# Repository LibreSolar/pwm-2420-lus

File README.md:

# PWM Solar Charge Controller (10-20A)

 Tested prototype, only minor issues left.

This PWM charge controller is cheaper than the MPPT charge controllers, as it does not contain the internal powerful DC/DC converter necessary for MPPT. The lower production cost and easy manufacturing with larger SMD components makes it ideally suited for solar home systems (SHS) for rural electrification.

The design allows to use either SMD MOSFETs or TO220 THT MOSFETs, which can be easily attached to a heat sink.

Schematic: [PDF file](pwm-2420-lus.pdf) in repository

Gerber files: [PCB ordering](http://libre.solar/docs/pcb_ordering) documentation

Bill of Materials: [BOM export](http://libre.solar/docs/bom) from KiCAD

Firmware: [Charge Controller Firmware](https://github.com/LibreSolar/charge-controller-firmware) repository

## Features:
- 12V/24V battery voltage
- Up to 20A max. charge current (depending on selected MOSFETs)
- 55V max. solar input
- 32bit ARM MCU (STM32L072)
- Expandable via Olimex Universal Extension Connector (UEXT) featuring
   I2C, Serial and SPI interface (e.g. used for display, WIFI communication, etc.)
- USB charging (single port)
- Low-side load switching

## Built-in protection
- Overvoltage
- Undervoltage
- Overcurrent
- PV short circuit
- PV reverse polarity (for max. module open circuit voltage of around 40V)
- Battery reverse polarity

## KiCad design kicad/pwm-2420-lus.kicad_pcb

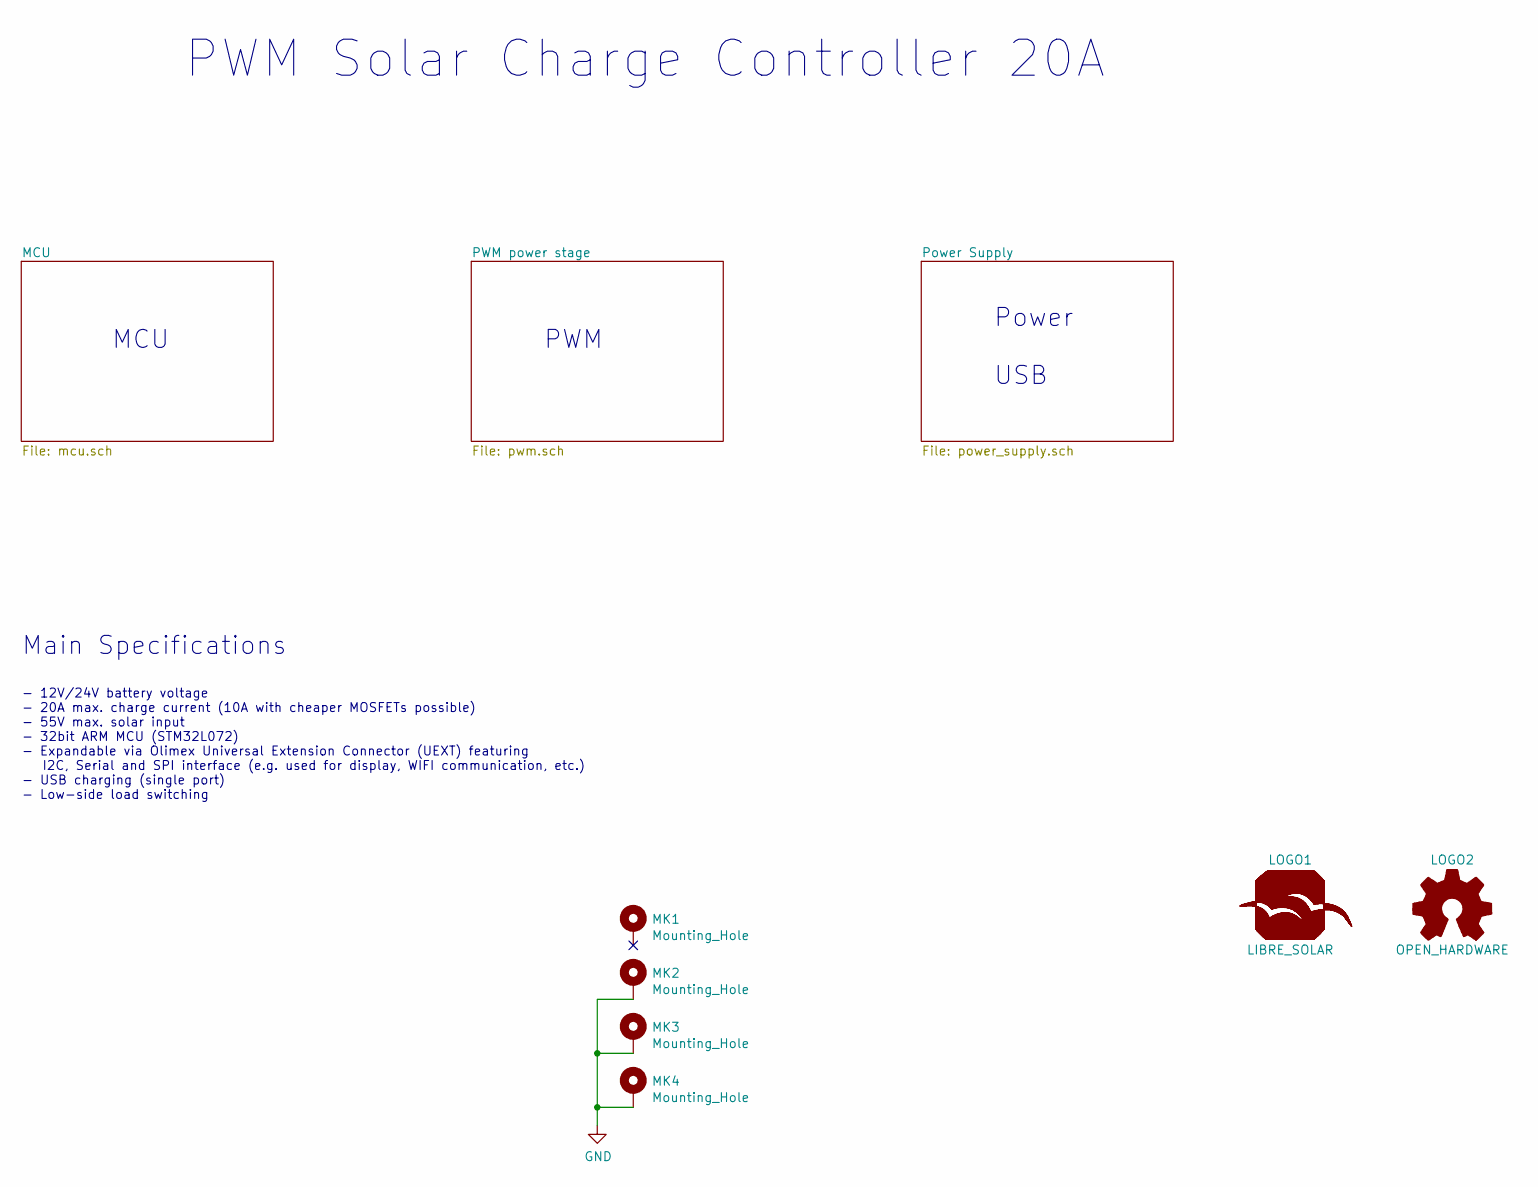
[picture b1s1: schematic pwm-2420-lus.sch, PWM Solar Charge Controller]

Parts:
LOGO1: LIBRE_SOLAR; LIBRESOLAR_LOGO
LOGO2: OPEN_HARDWARE; OSHW-Logo_5.7x6mm_SilkScreen
MK1, MK2, MK3, MK4: Mounting_Hole; MountingHole_3.2mm_M3_Pad

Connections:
GND: MK2.1, MK3.1, MK4.1; also elsewhere on the board

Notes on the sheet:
PWM Solar Charge Controller 20A
Main Specifications
- 12V/24V battery voltage - 20A max. charge current (10A with cheaper MOSFETs possible) - 55V max. solar input - 32bit ARM MCU (STM32L072) - Expandable via Olimex Universal Extension Connector (UEXT) featuring I2C, Serial and SPI interface (e.g. used for display, WIFI communication, etc.) - USB cha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
PWM
MCU
Power USB

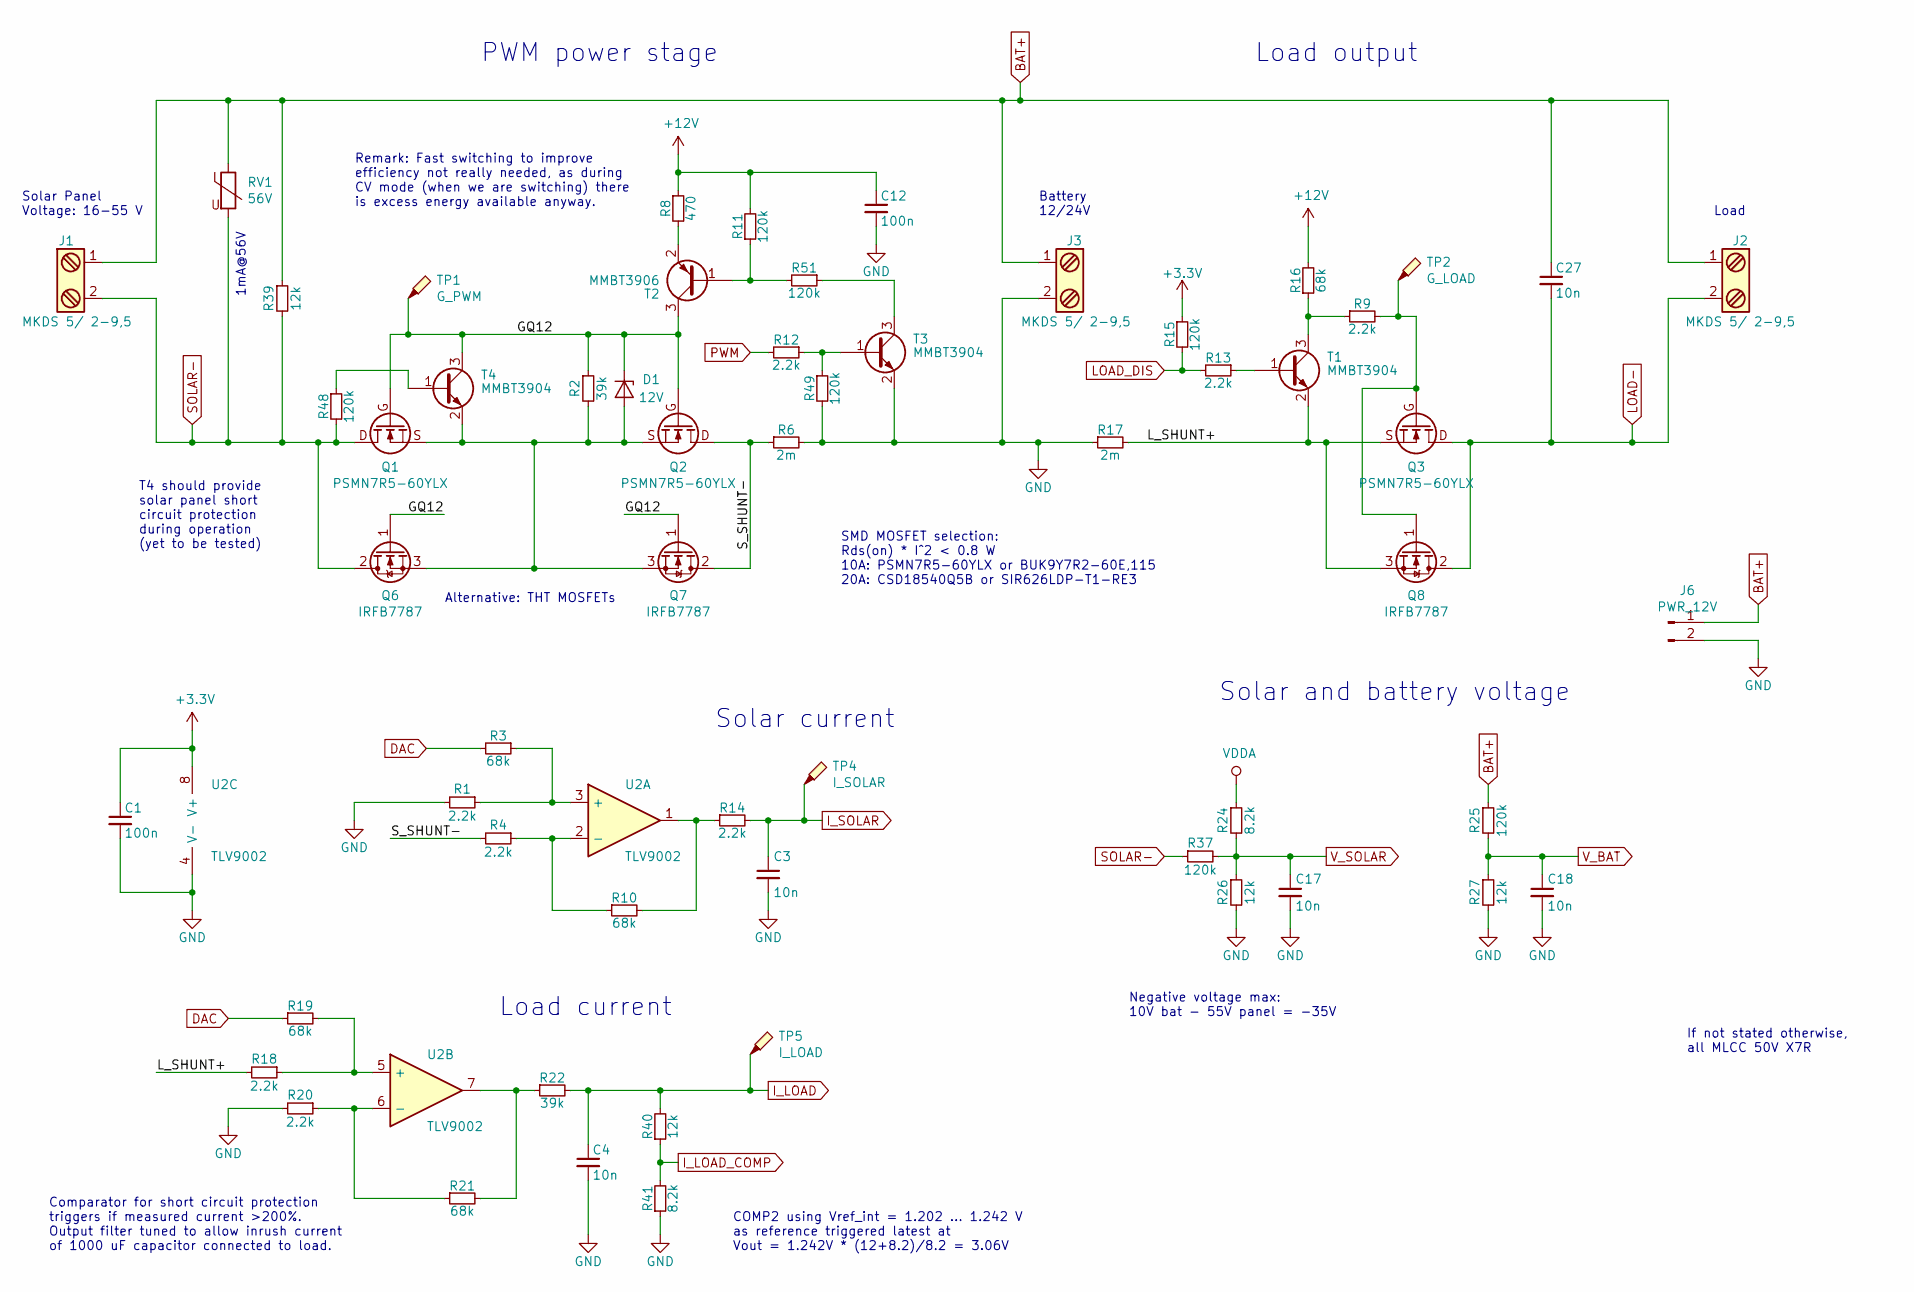
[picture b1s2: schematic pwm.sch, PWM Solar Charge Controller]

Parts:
C1, C12: 100n; C_0805_2012; PartNumber CC0805KRX7R9BB104
C3, C4, C17, C18, C27: 10n; C_0805_2012; PartNumber CC0805KRX7R0BB103
D1: 12V; D_SOT-23_ANK; PartNumber SZBZX84C12LT3G
J1, J2, J3: MKDS 5/ 2-9,5; Phoenix_Contact_MKDS_5-2-952; PartNumber 1714971
J6: PWR_12V; JST_XH_B02B-XH-A_1x02_P2.50mm_Vertical; PartNumber B2B-XH-A (LF)(SN)
Q1, Q2, Q3: PSMN7R5-60YLX; 5X6_MOSFET; PartNumber PSMN7R5-60YLX
Q6, Q7, Q8: IRFB7787; TO-220-3_Horizontal_TabUp; PartNumber IRFB7787PbF
R1, R4, R9, R12, R13, R14, R18, R20: 2.2k; R_0805_2012; PartNumber RC0805FR-072K2L
R2: 39k; R_0805_2012; PartNumber RC0805FR-0739KL
R3, R10, R16, R19, R21: 68k; R_0805_2012; PartNumber RC0805FR-0768KL
R6, R17: 2m; R_Bourns_CRE2512; PartNumber CRE2512-FZ-R002E-3
R8: 470; R_0805_2012; PartNumber RC0805FR-07470RL
R11, R15, R25, R37, R48, R49, R51: 120k; R_0805_2012; PartNumber RC0805FR-07120KL
R22: 39k; R_0805_2012; PartNumber RC0805FR-0739K0L
R24, R41: 8.2k; R_0805_2012; PartNumber RC0805FR-078K2L
R26, R27, R39, R40: 12k; R_0805_2012; PartNumber RC0805FR-0712KL
RV1: 56V; RV_Disc_D12mm_W4.3mm_P7.5mm; PartNumber MOV-10D560K
T1, T3, T4: MMBT3904; SOT-23; PartNumber MMBT3904-7-F
T2: MMBT3906; SOT-23; PartNumber MMBT3906-7-F
TP1: G_PWM; TestPoint_Pad_D1.0mm
TP2: G_LOAD; TestPoint_Pad_D1.0mm
TP4: I_SOLAR; TestPoint_Pad_D1.0mm
TP5: I_LOAD; TestPoint_Pad_D1.0mm
U2: TLV9002; SOIC-8_3.9x4.9mm_Pitch1.27mm; PartNumber LM258DR

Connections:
+3V3: C1.1, R15.1, U2.8 (V+); also elsewhere on the board
+12V: C12.1, R8.1, R11.2, R16.2; also elsewhere on the board
/PWM power stage/GQ12: D1.1 (K), Q1.G, Q2.G, Q6.1 (G), Q7.1 (G), R2.1, T2.3 (C), T4.3 (C), TP1.1
/PWM power stage/L_SHUNT+: Q3.S, Q8.3 (S), R17.2, R18.2, T1.2 (E)
/PWM power stage/S_SHUNT-: Q2.D, Q7.2 (D), R4.2, R6.1
BAT+: C27.1, J1.1, J2.1, J3.1, J6.1, R25.1, R39.1, RV1.1; also elsewhere on the board
DAC: R3.2, R19.1; also elsewhere on the board
GND: C1.2, C3.2, C4.2, C12.2, C17.2, C18.2, J3.2, J6.2, R1.2, R6.2, R17.1, R20.2, R26.2, R27.2, R41.1, R49.2, T3.2 (E), U2.4 (V-); also elsewhere on the board
I_LOAD: C4.1, R22.2, R40.2, TP5.1; also elsewhere on the board
I_LOAD_COMP: R40.1, R41.2; also elsewhere on the board
I_SOLAR: C3.1, R14.2, TP4.1; also elsewhere on the board
LOAD-: C27.2, J2.2, Q3.D, Q8.2 (D); also elsewhere on the board
LOAD_DIS: R13.2, R15.2; also elsewhere on the board
unnamed: D1.2 (A), Q1.S, Q2.S, Q6.3 (S), Q7.3 (S), R2.2, T4.2 (E)
unnamed: Q3.G, Q8.1 (G), R9.2, TP2.1
unnamed: R1.1, R3.1, U2.3 (+)
unnamed: R8.2, T2.2 (E)
unnamed: R4.1, R10.1, U2.2 (-)
unnamed: R10.2, R14.1, U2.1
unnamed: R11.1, R51.2, T2.1 (B)
unnamed: R12.1, R49.1, T3.1 (B)
unnamed: R13.1, T1.1 (B)
unnamed: R9.1, R16.1, T1.3 (C)
unnamed: R18.1, R19.2, U2.5 (+)
unnamed: R20.1, R21.1, U2.6 (-)
unnamed: R21.2, R22.1, U2.7
unnamed: R48.1, T4.1 (B)
unnamed: R51.1, T3.3 (C)
PWM: R12.2; also elsewhere on the board
SOLAR-: J1.2, Q1.D, Q6.2 (D), R37.1, R39.2, R48.2, RV1.2
VDDA: R24.1; also elsewhere on the board
V_BAT: C18.1, R25.2, R27.1; also elsewhere on the board
V_SOLAR: C17.1, R24.2, R26.1, R37.2; also elsewhere on the board

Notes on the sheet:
Solar Panel Voltage: 16-55 V
PWM power stage
Load output
If not stated otherwise, all MLCC 50V X7R
Solar and battery voltage
SMD MOSFET selection: Rds(on) * I^2 < 0.8 W 10A: PSMN7R5-60YLX or BUK9Y7R2-60E,115 20A: CSD18540Q5B or SIR626LDP-T1-RE3
Remark: Fast switching to improve efficiency not really needed, as during CV mode (when we are switching) there is excess energy available anyway.
1mA@56V
Load current
Solar current
Negative voltage max: 10V bat - 55V panel = -35V
Comparator for short circuit protection triggers if measured current >200%. Output filter tuned to allow inrush current of 1000 uF capacitor connected to load.
Alternative: THT MOSFETs
COMP2 using Vref_int = 1.202 ... 1.242 V as reference triggered latest at Vout = 1.242V * (12+8.2)/8.2 = 3.06V
Battery 12/24V
Load
T4 should provide solar panel short circuit protection during operation (yet to be tested)

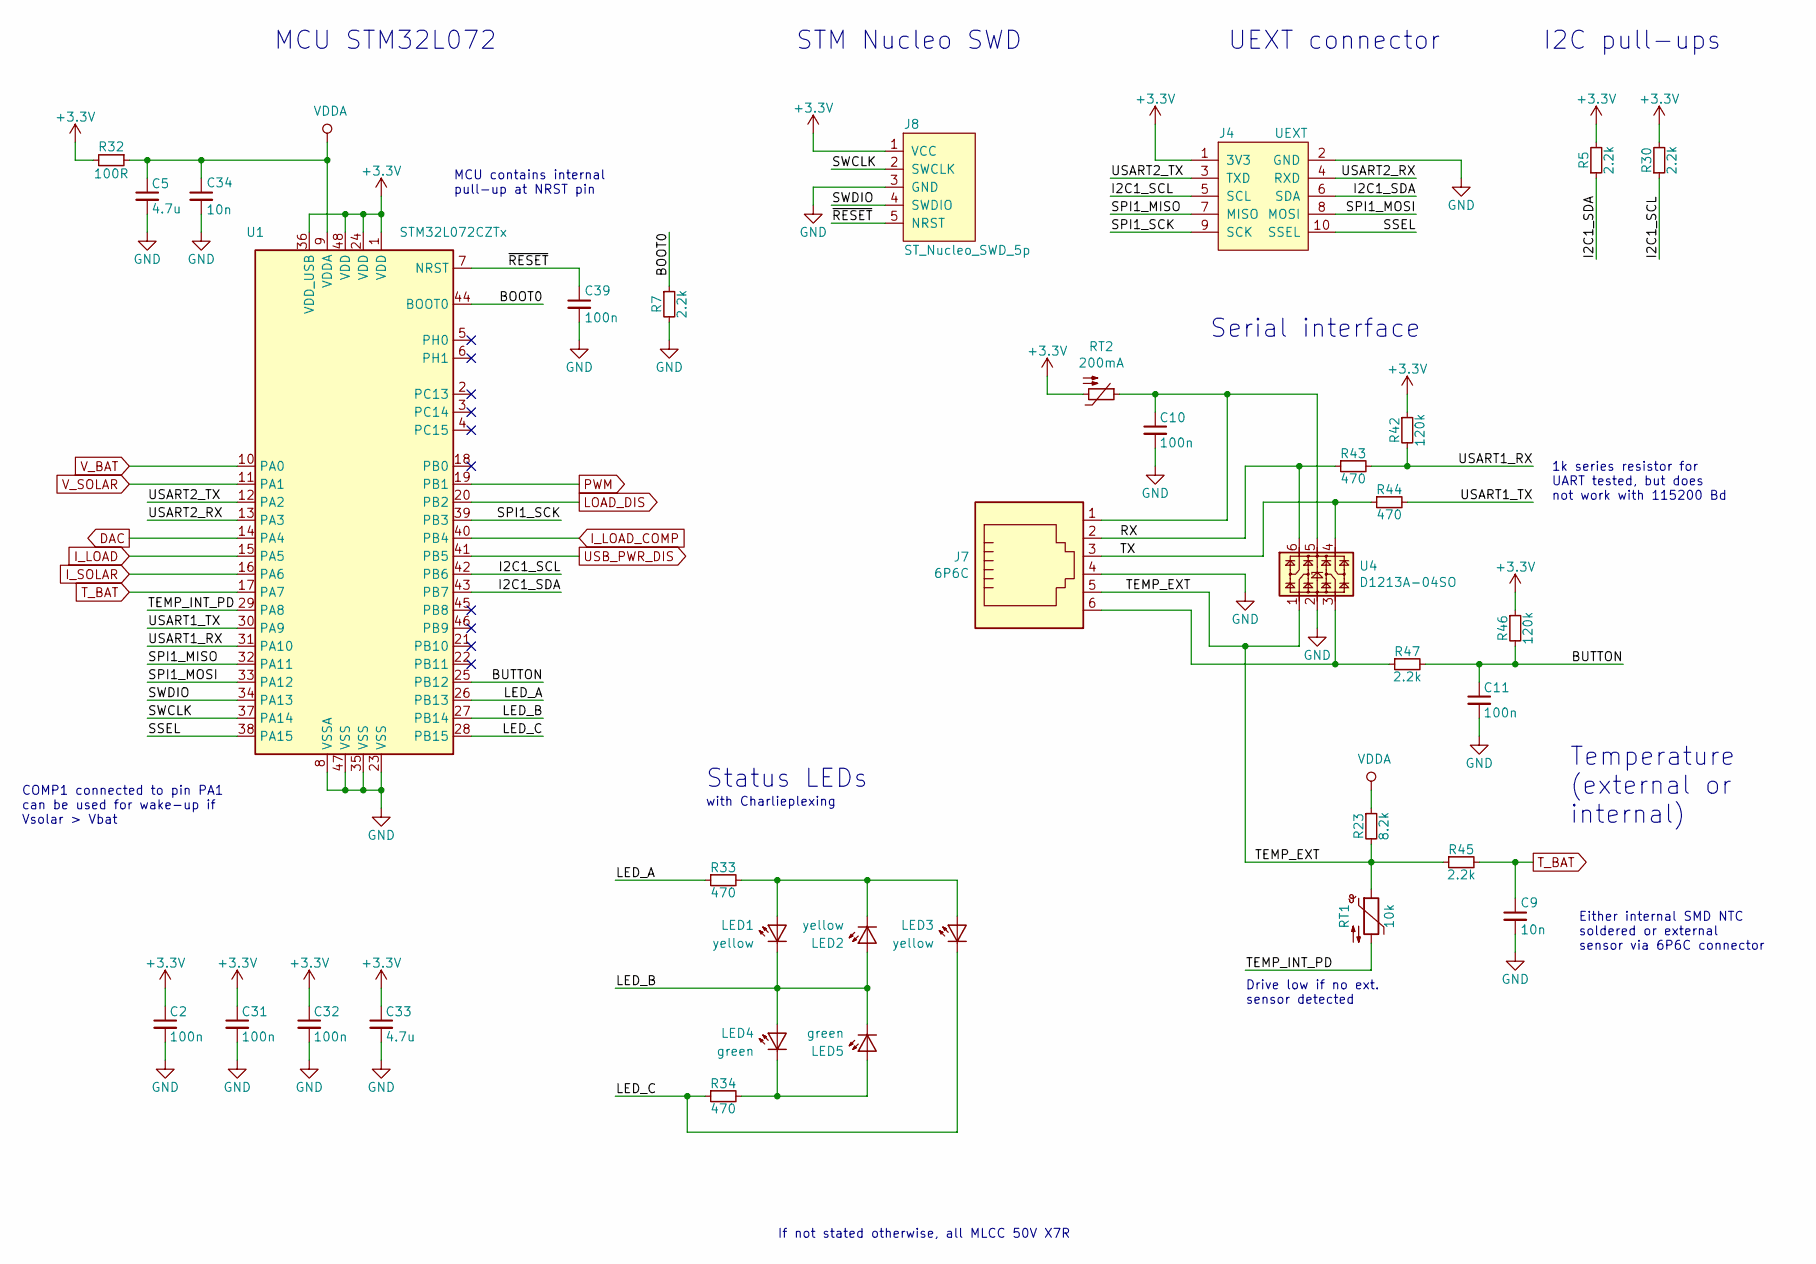
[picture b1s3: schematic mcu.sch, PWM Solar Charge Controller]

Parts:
C2, C10, C11, C31, C32, C39: 100n; C_0805_2012; PartNumber CC0805KRX7R9BB104
C5, C33: 4.7u; C_0805_2012; PartNumber 885012107018
C9, C34: 10n; C_0805_2012; PartNumber CC0805KRX7R0BB103
J4: UEXT; Box_Header_2x05x2.54mm_Straight; PartNumber 302-S101
J7: 6P6C; RJ25_6P6C_TabUp; PartNumber 615006138421
J8: ST_Nucleo_SWD_5p; PinHeader_1x05_P2.54mm_Vertical
LED1, LED3: yellow; LED_0603_D3.0mm; PartNumber LTL-1CHY
LED2, LED5: green; LED_0603_D3.0mm; PartNumber LTL-4231
R5, R7, R30, R45, R47: 2.2k; R_0805_2012; PartNumber RC0805FR-072K2L
R23: 8.2k; R_0805_2012; PartNumber RC0805FR-078K2L
R32: 100R; R_0805_2012; PartNumber RC0805FR-07100RL
R33, R34, R43, R44: 470; R_0805_2012; PartNumber RC0805FR-07470RL
R42, R46: 120k; R_0805_2012; PartNumber RC0805FR-07120KL
RT1: 10k; R_0805_2012; PartNumber NCP21XV103J03RA
RT2: 200mA; R_1206_3216; PartNumber 0ZCJ0020FF2E
U1: STM32L072CZTx; LQFP-48_7x7mm_P0.5mm; PartNumber STM32L072CZT6
U4: D1213A-04SO; SOT-23-6; PartNumber D1213A-04SO

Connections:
+3V3: C2.1, C31.1, C32.1, C33.1, J4.1 (3V3), J8.1 (VCC), R5.2, R30.2, R32.2, R42.1, R46.1, RT2.2, U1.1 (VDD), U1.24 (VDD), U1.36 (VDD_USB), U1.48 (VDD); also elsewhere on the board
/MCU/BOOT0: R7.1, U1.44 (BOOT0)
/MCU/BUTTON: C11.1, R46.2, R47.2, U1.25 (PB12)
/MCU/I2C1_SCL: J4.5 (SCL), R30.1, U1.42 (PB6)
/MCU/I2C1_SDA: J4.6 (SDA), R5.1, U1.43 (PB7)
/MCU/LED_A: R33.1, U1.26 (PB13)
/MCU/LED_B: LED1.1 (K), LED2.2 (A), LED5.1 (K), U1.27 (PB14); also elsewhere on the board
/MCU/LED_C: LED3.1 (K), R34.1, U1.28 (PB15)
/MCU/RX: J7.2, R43.1, U4.6
/MCU/SPI1_MISO: J4.7 (MISO), U1.32 (PA11)
/MCU/SPI1_MOSI: J4.8 (MOSI), U1.33 (PA12)
/MCU/SPI1_SCK: J4.9 (SCK), U1.39 (PB3)
/MCU/SSEL: J4.10 (SSEL), U1.38 (PA15)
/MCU/SWCLK: J8.2 (SWCLK), U1.37 (PA14)
/MCU/SWDIO: J8.4 (SWDIO), U1.34 (PA13)
/MCU/TEMP_EXT: J7.5, R23.2, R45.1, RT1.1, U4.1
/MCU/TEMP_INT_PD: RT1.2, U1.29 (PA8)
/MCU/TX: J7.3, R44.1, U4.4
/MCU/USART1_RX: R42.2, R43.2, U1.31 (PA10)
/MCU/USART1_TX: R44.2, U1.30 (PA9)
/MCU/USART2_RX: J4.4 (RXD), U1.13 (PA3)
/MCU/USART2_TX: J4.3 (TXD), U1.12 (PA2)
/MCU/~RESET: C39.1, J8.5 (NRST), U1.7 (NRST)
DAC: U1.14 (PA4); also elsewhere on the board
GND: C2.2, C5.2, C9.2, C10.2, C11.2, C31.2, C32.2, C33.2, C34.2, C39.2, J4.2 (GND), J7.4, J8.3 (GND), R7.2, U1.8 (VSSA), U1.23 (VSS), U1.35 (VSS), U1.47 (VSS), U4.2; also elsewhere on the board
I_LOAD: U1.15 (PA5); also elsewhere on the board
I_LOAD_COMP: U1.40 (PB4); also elsewhere on the board
I_SOLAR: U1.16 (PA6); also elsewhere on the board
LOAD_DIS: U1.20 (PB2); also elsewhere on the board
unnamed: C10.1, J7.1, RT2.1, U4.5
unnamed: J7.6, R47.1, U4.3
PWM: U1.19 (PB1); also elsewhere on the board
T_BAT: C9.1, R45.2, U1.17 (PA7)
USB_PWR_DIS: U1.41 (PB5); also elsewhere on the board
VDDA: C5.1, C34.1, R23.1, R32.1, U1.9 (VDDA); also elsewhere on the board
V_BAT: U1.10 (PA0); also elsewhere on the board
V_SOLAR: U1.11 (PA1); also elsewhere on the board

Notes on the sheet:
Status LEDs
MCU STM32L072
STM Nucleo SWD
If not stated otherwise, all MLCC 50V X7R
UEXT connector
I2C pull-ups
MCU contains internal pull-up at NRST pin
with Charlieplexing
Temperature (external or internal)
Either internal SMD NTC soldered or external sensor via 6P6C connector
Serial interface
COMP1 connected to pin PA1 can be used for wake-up if Vsolar > Vbat
Drive low if no ext. sensor detected
1k series resistor for UART tested, but does not work with 115200 Bd

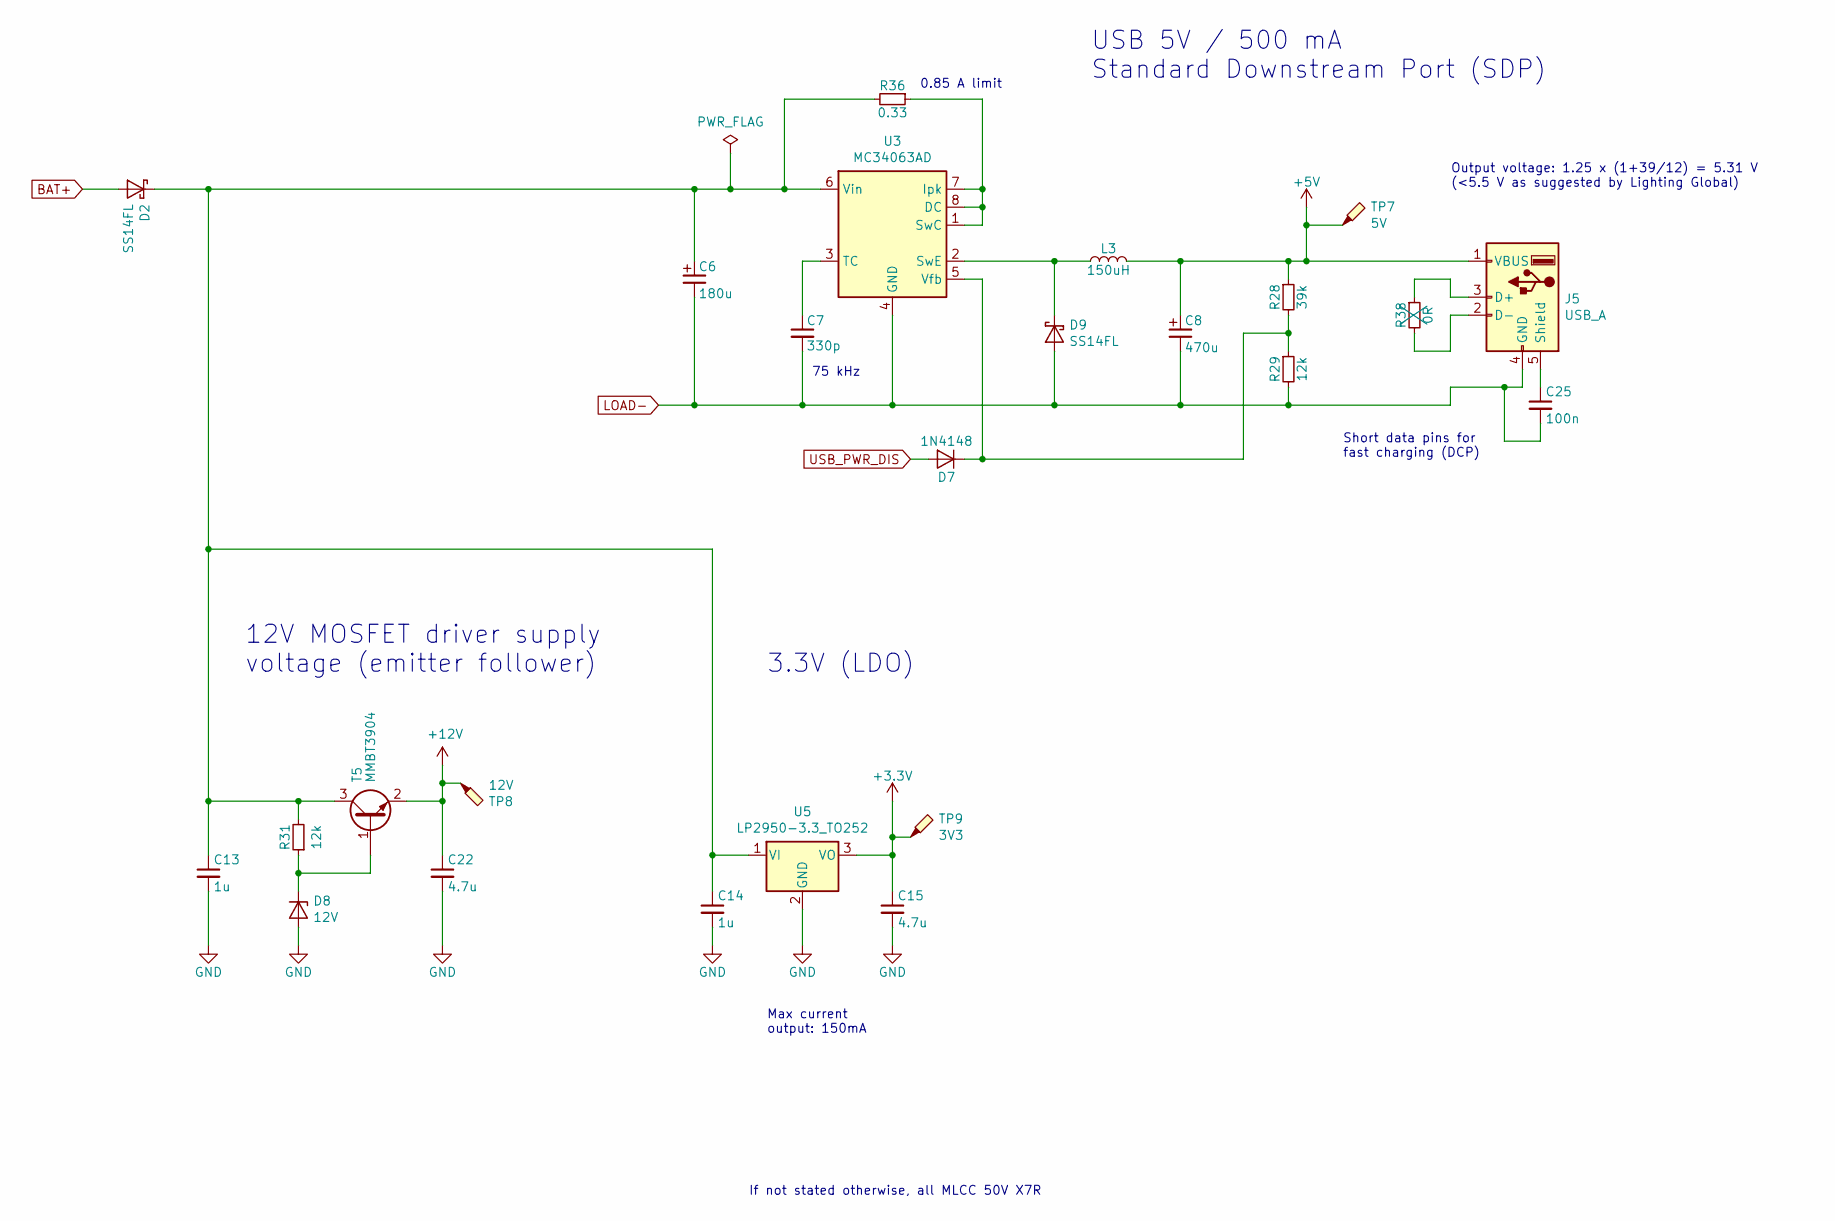
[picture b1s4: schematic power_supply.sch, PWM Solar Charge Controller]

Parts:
C6: 180u; CP_Radial_D8.0mm_P3.50mm; PartNumber EEU-FR1V181
C7: 330p; C_0805_2012; PartNumber 885342007002
C8: 470u; CP_Radial_D8.0mm_P3.50mm; PartNumber EEUFR1A471
C13, C14: 1u; C_0805_2012; PartNumber CC0805KKX7R9BB105
C15, C22: 4.7u; C_0805_2012; PartNumber 885012107018
C25: 100n; C_0805_2012; PartNumber CC0805KRX7R9BB104
D2, D9: SS14FL; D_SOD-123F; PartNumber SS14FL
D7: 1N4148; D_SOD-123; PartNumber 1N4148W-7-F
D8: 12V; D_SOT-23_ANK; PartNumber SZBZX84C12LT3G
J5: USB_A; USB_A_Wuerth_61400416021_Horizontal; PartNumber 61400416021
L3: 150uH; L_Radial_D12.0mm_P5.00mm_Fastron_11P; PartNumber RLB0914-151KL
R28: 39k; R_0805_2012; PartNumber RC0805FR-0739KL
R29, R31: 12k; R_0805_2012; PartNumber RC0805FR-0712KL
R36: 0.33; R_1206_3216; PartNumber RL1206FR-070R33L
R38: 0R; R_0805_2012; PartNumber RC0805FR-070RL
T5: MMBT3904; SOT-23; PartNumber MMBT3904-7-F
TP7: 5V; TestPoint_Pad_D1.0mm
TP8: 12V; TestPoint_Pad_D1.0mm
TP9: 3V3; TestPoint_Pad_D1.0mm
U3: MC34063AD; SOIC-8_3.9x4.9mm_P1.27mm; PartNumber MC34063ADR
U5: LP2950-3.3_TO252; TO-252-2; PartNumber LP2950ACDT-3.3RG

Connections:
+3V3: C15.1, TP9.1, U5.3 (VO); also elsewhere on the board
+5V: C8.1, J5.1 (VBUS), L3.2, R28.1, TP7.1
+12V: C22.1, T5.2 (E), TP8.1; also elsewhere on the board
BAT+: D2.2 (A); also elsewhere on the board
GND: C13.2, C14.2, C15.2, C22.2, D8.2 (A), U5.2 (GND); also elsewhere on the board
LOAD-: C6.2, C7.2, C8.2, C25.2, D9.2 (A), J5.4 (GND), R29.2, U3.4 (GND); also elsewhere on the board
unnamed: C7.1, U3.3 (TC)
unnamed: C6.1, C13.1, C14.1, D2.1 (K), R31.2, R36.2, T5.3 (C), U3.6 (Vin), U5.1 (VI)
unnamed: C25.1, J5.5 (Shield)
unnamed: D7.1 (K), R28.2, R29.1, U3.5 (Vfb)
unnamed: D8.1 (K), R31.1, T5.1 (B)
unnamed: D9.1 (K), L3.1, U3.2 (SwE)
unnamed: J5.2 (D-), R38.2
unnamed: J5.3 (D+), R38.1
unnamed: R36.1, U3.1 (SwC), U3.7 (Ipk), U3.8 (DC)
USB_PWR_DIS: D7.2 (A); also elsewhere on the board

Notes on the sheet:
Max current output: 150mA
USB 5V / 500 mA Standard Downstream Port (SDP)
3.3V (LDO)
If not stated otherwise, all MLCC 50V X7R
Output voltage: 1.25 x (1+39/12) = 5.31 V (<5.5 V as suggested by Lighting Global)
12V MOSFET driver supply voltage (emitter follower)
Short data pins for fast charging (DCP)
75 kHz
0.85 A limit

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
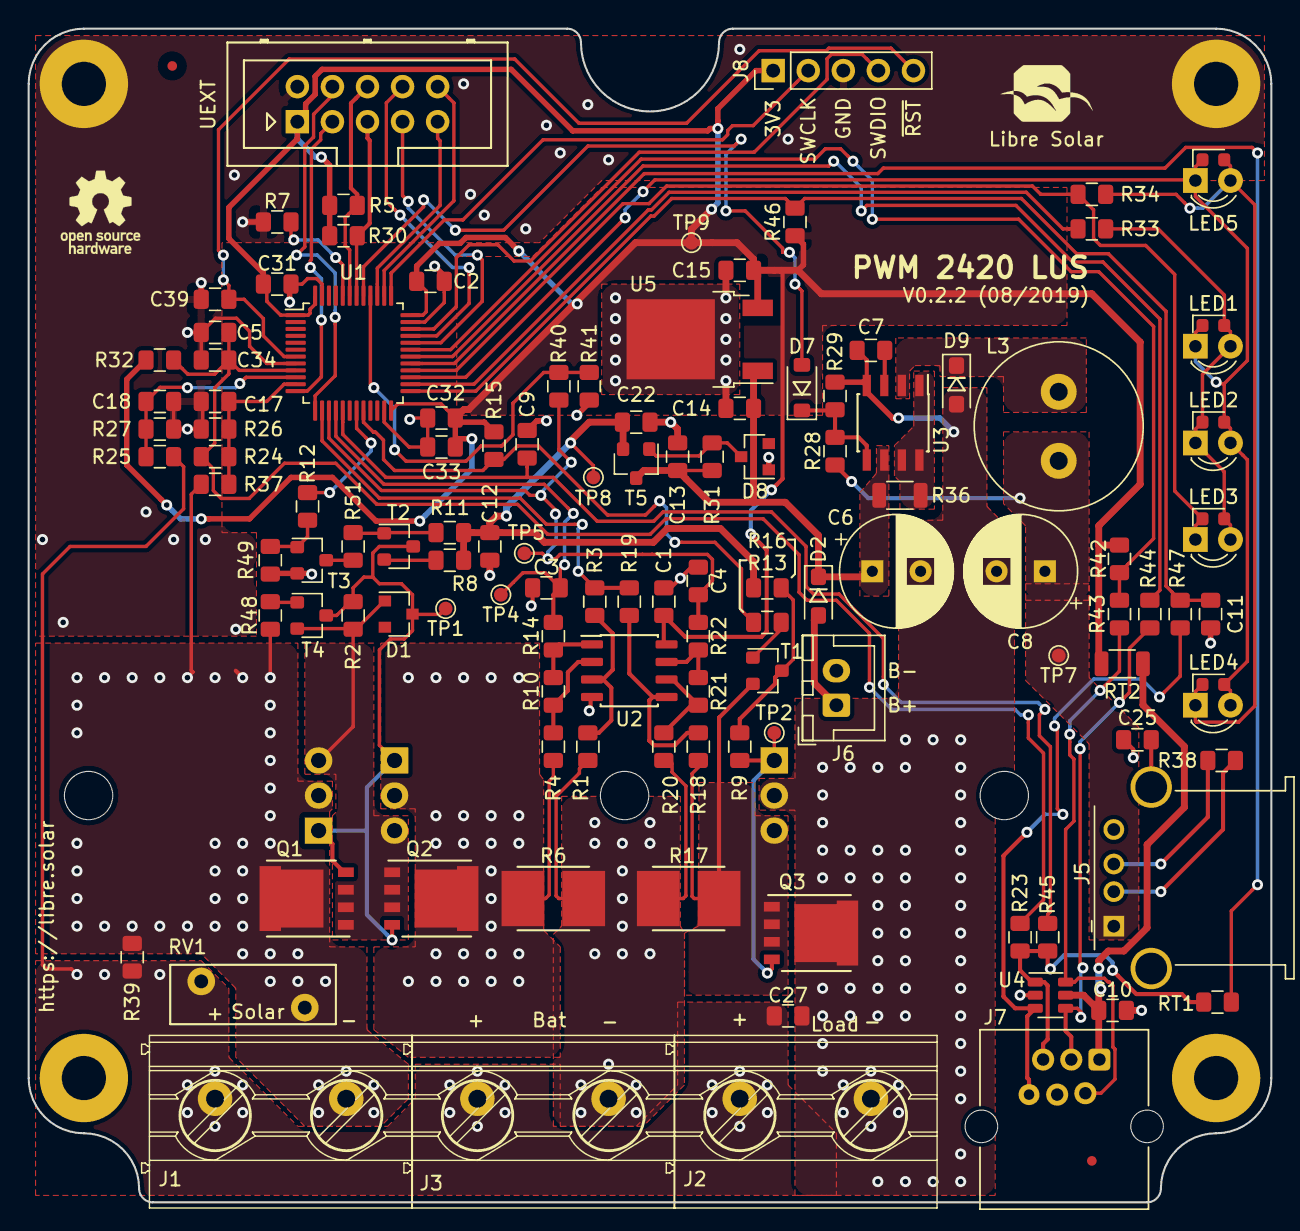
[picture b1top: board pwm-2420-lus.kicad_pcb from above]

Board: 2 copper layers, 90.0 x 85.0 mm, 125 parts (0 on the bottom side), 71 nets.

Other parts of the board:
LED4: green; LED_0603_D3.0mm

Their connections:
/MCU/LED_B: LED4.2; also elsewhere on the board

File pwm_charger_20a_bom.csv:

Component,Description,Part,References,Value,Footprint,Quantity Per PCB,Datasheet,PartNumber,Manufacturer,Remarks,Config,DNP
1,Unpolarized capacitor,C,C1 C2 C10 C11 C12 C25 C31 C32 C39,100n,C_0805_2012,9,,CC0805KRX7R9BB104,Yageo,,,
2,Unpolarized capacitor,C,C3 C4 C9 C17 C18 C27 C34,10n,C_0805_2012,7,,CC0805KRX7R0BB103,Yageo,"100V, X7R",,
3,Polarised capacitor,CP,C6,180u,CP_Radial_D8.0mm_P3.50mm,1,,EEU-FR1V181,Panasonic,35V,,
4,Unpolarized capacitor,C,C13 C14,1u,C_0805_2012,2,,CC0805KKX7R9BB105,Yageo,"50V, X7R",,
5,Unpolarized capacitor,C,C7,330p,C_0805_2012,1,,885342007002,Wurth Electronics,"50V, C0G (NP0)",,
6,Unpolarized capacitor,C,C5 C15 C22 C33,4.7u,C_0805_2012,4,,885012107018,Wurth Electronics,"25V, X5R",,
7,Polarised capacitor,CP,C8,470u,CP_Radial_D8.0mm_P3.50mm,1,,EEUFR1A471,Panasonic,10V,,
8,Diode zener,D_Zener,D1 D8,12V,D_SOT-23_ANK,2,,SZBZX84C12LT3G,ON Semiconductor,Alternative: Diodes Inc. BZX84C12-7-F,,
9,Diode,D,D7,1N4148,D_SOD-123,1,,1N4148W-7-F,Diodes Inc.,,,
10,Diode Schottky,D_Schottky,D2 D9,SS14FL,D_SOD-123F,2,,SS14FL,On Semiconductor,,,
11,"RJ connector, 6P6C (6 positions 6 connected), RJ12/RJ18/RJ25",6P6C,J7,6P6C,RJ25_6P6C_TabUp,1,,615006138421,Wurth Electronics,Alternative: Pulse E5566-Q0LK22-L,,
12,,Screw_Terminal_1x02,J1 J2 J3,"MKDS 5/ 2-9,5",Phoenix_Contact_MKDS_5-2-952,3,,1714971,Phoenix Contact,,,
13,"Generic connector, single row, 01x02, script generated (kicad-library-utils/schlib/autogen/connector/)",Conn_01x02_Male,J6,PWR_12V,JST_XH_B02B-XH-A_1x02_P2.50mm_Vertical,1,~,B2B-XH-A (LF)(SN),JST,,,
14,,ST_Nucleo_SWD_5p,J8,ST_Nucleo_SWD_5p,PinHeader_1x05_P2.54mm_Vertical,1,,,any,"1x5 pin header, pitch 2.54 mm",,
15,,UEXT,J4,UEXT,Box_Header_2x05x2.54mm_Straight,1,,,any,"2x5 pin box header, pitch 2.54 mm",,
16,USB Type A connector,USB_A,J5,USB_A,USB_A_Wuerth_61400416021_Horizontal,1, ~,61400416021,Wurth Electronics,,,
17,Inductor,L,L3,150uH,L_Radial_D12.0mm_P5.00mm_Fastron_11P,1,,RLB0914-151KL,Bourns,,,
18,,D_LED,LED4 LED5,green,LED_D3.0mm,2,,LTL-4231,Lite-On,Green LED 3mm,,
19,,D_LED,LED1 LED2 LED3,yellow,LED_D3.0mm,3,,LTL-1CHY,Lite-On,Yellow LED 3mm,,
20,Transistor N-MOSFET (general),Q_NMOS,Q1 Q2 Q3,PSMN7R5-60YLX,5X6_MOSFET,3,~,PSMN7R5-60YLX,Nexperia,,,
21,Resistor,R,R36,0.33,R_1206_3216,1,,RL1206FR-070R33L,Yageo,,,
22,Resistor,R,R32,100R,R_0805_2012,1,,RC0805FR-07100RL,Yageo,,,
23,Resistor,R,R11 R15 R25 R37 R42 R46 R48 R49 R51,120k,R_0805_2012,9,,RC0805FR-07120KL,Yageo,,,
24,Resistor,R,R26 R27 R29 R31 R39 R40,12k,R_0805_2012,6,,RC0805FR-0712KL,Yageo,,,
25,Resistor,R,R1 R4 R5 R7 R9 R12 R13 R14 R18 R20 R22 R30 R45 R47,2.2k,R_0805_2012,14,,RC0805FR-072K2L,Yageo,,,
26,Resistor,R,R6 R17,2m,R_Bourns_CRE2512,2,,CRE2512-FZ-R002E-3,Bourns,,,
27,Resistor,R,R2 R28,39k,R_0805_2012,2,,RC0805FR-0739KL,Yageo,,,
28,Resistor,R,R8 R33 R34 R43 R44,470,R_0805_2012,5,,RC0805FR-07470RL,Yageo,,,
29,Resistor,R,R3 R10 R16 R19 R21,68k,R_0805_2012,5,,RC0805FR-0768KL,Yageo,,,
30,Resistor,R,R23 R24 R41,8.2k,R_0805_2012,3,,RC0805FR-078K2L,Yageo,,,
31,"Temperature dependent resistor, negative temperature coefficient",Thermistor_NTC,RT1,10k,R_0805_2012,1,,NCP21XV103J03RA,Murata,,,
32,,R_PTC,RT2,200mA,R_1206_3216,1,,0ZCJ0020FF2E,Bel,,,
33,Voltage dependent resistor,Varistor,RV1,56V,RV_Disc_D12mm_W4.3mm_P7.5mm,1,,MOV-10D560K,Bourns,,,
34,"0.8A Ic, 45V Vce, NPN Transistor, SOT-23",BC817,T1 T4 T5,MMBT3904,SOT-23,3,http://www.fairchildsemi.com/ds/BC/BC817.pdf,MMBT3904-7-F,Diodes Inc.,,,
35,"0.2A Ic, 40V Vce, Small Signal NPN Transistor, SOT-23",MMBT3904,T3,MMBT3904,SOT-23,1,http://www.fairchildsemi.com/ds/BC/BC817.pdf,MMBT3904-7-F,Diodes Inc.,,,
36,"-0.2A Ic, -40V Vce, Small Signal PNP Transistor, SOT-23",MMBT3906,T2,MMBT3906,SOT-23,1,http://www.fairchildsemi.com/ds/BC/BC807.pdf,MMBT3906-7-F,Diodes Inc.,,,
37,"Transient voltage suppressor designed to protect high speed data lines from ESD, EFT, and lightning",NUP4202,U4,D1213A-04SO,SOT-23-6,1,http://www.onsemi.com/pub_link/Collateral/NUP4202W1-D.PDF,D1213A-04SO,Diodes Inc.,Alternative: IP4220CZ6,,
38,"Positive 100mA 30V Linear Micropower Voltage Regulator, Fixed Output 3.3V, TO-252",LP2950-3.3_TO252,U5,LP2950-3.3_TO252,TO-252-2,1,http://www.ti.com/lit/ds/symlink/lp2950-n.pdf,LP2950ACDT-3.3RG,ON Semiconductor,,,
39,"1.5A, step-up/down/inverting switching regulator, 3-40V Vin, 100kHz, SO-8",MC34063AD,U3,MC34063AD,SOIC-8_3.9x4.9mm_P1.27mm,1,http://www.onsemi.com/pub_link/Collateral/MC34063A-D.PDF,MC34063ADR,Texas Instruments,,,
40,"ARM Cortex-M0+ MCU, 192KB flash, 20KB RAM, 32MHz, 1.65-3.6V, 37 GPIO, LQFP-48",STM32L072CZTx,U1,STM32L072CZTx,LQFP-48_7x7mm_P0.5mm,1,http://www.st.com/st-web-ui/static/active/en/resource/techni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,STM32L072CZT6,ST Microelectronics,Alternative: STM32L073CZT6,,
41,Dual operational amplifier,Opamp_Dual_Generic,U2,TLV9002,SOIC-8_3.9x4.9mm_Pitch1.27mm,1,,TLV9002IDR,Texas Instruments,Alternatives: MCP6002T-I/SN or TLV6002IDR,,





Component Groups:,43
Component Count:,112
Fitted Components:,108
Number of PCBs:,1
Total components:,108
Schematic Version:,0.2
Schematic Date:,2019-03-05
BoM Date:,Mi 13 Mr 2019 10:07:07 CET
Schematic Source:,/home/martin/LibreSolar/2_Development/04_Hardware/PWM-Charger_20A/pwm_charger_20a.sch
KiCad Version:,Eeschema 5.0.1

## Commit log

2019-04-26 Updates after manufacturer feedback
2019-08-15 Folder restructured and files renamed
2019-08-16 Load current sense filter and comparator updated
2019-08-26 Improved power supply and exposed BOOT0 pin
    - BOOT0 pin connected to BUTTON wire to allow firmware upgrade via LS.one port
    - Additional emitter follower for 3V3 power supply to increase margin to 30V absolute max. rating of LDO in case of 24V battery
    - Corners adjusted to match shape of MPPT 1210 HUS
